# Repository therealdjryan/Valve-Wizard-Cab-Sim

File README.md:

# Valve-Wizard-Cab-Sim
http://valvewizard.co.uk/cabsim.html

[HTML BOM Viewer](https://htmlpreview.github.io/?https://raw.githubusercontent.com/therealdjryan/Valve-Wizard-Cab-Sim/main/fab/htmlbom/ibom.html)

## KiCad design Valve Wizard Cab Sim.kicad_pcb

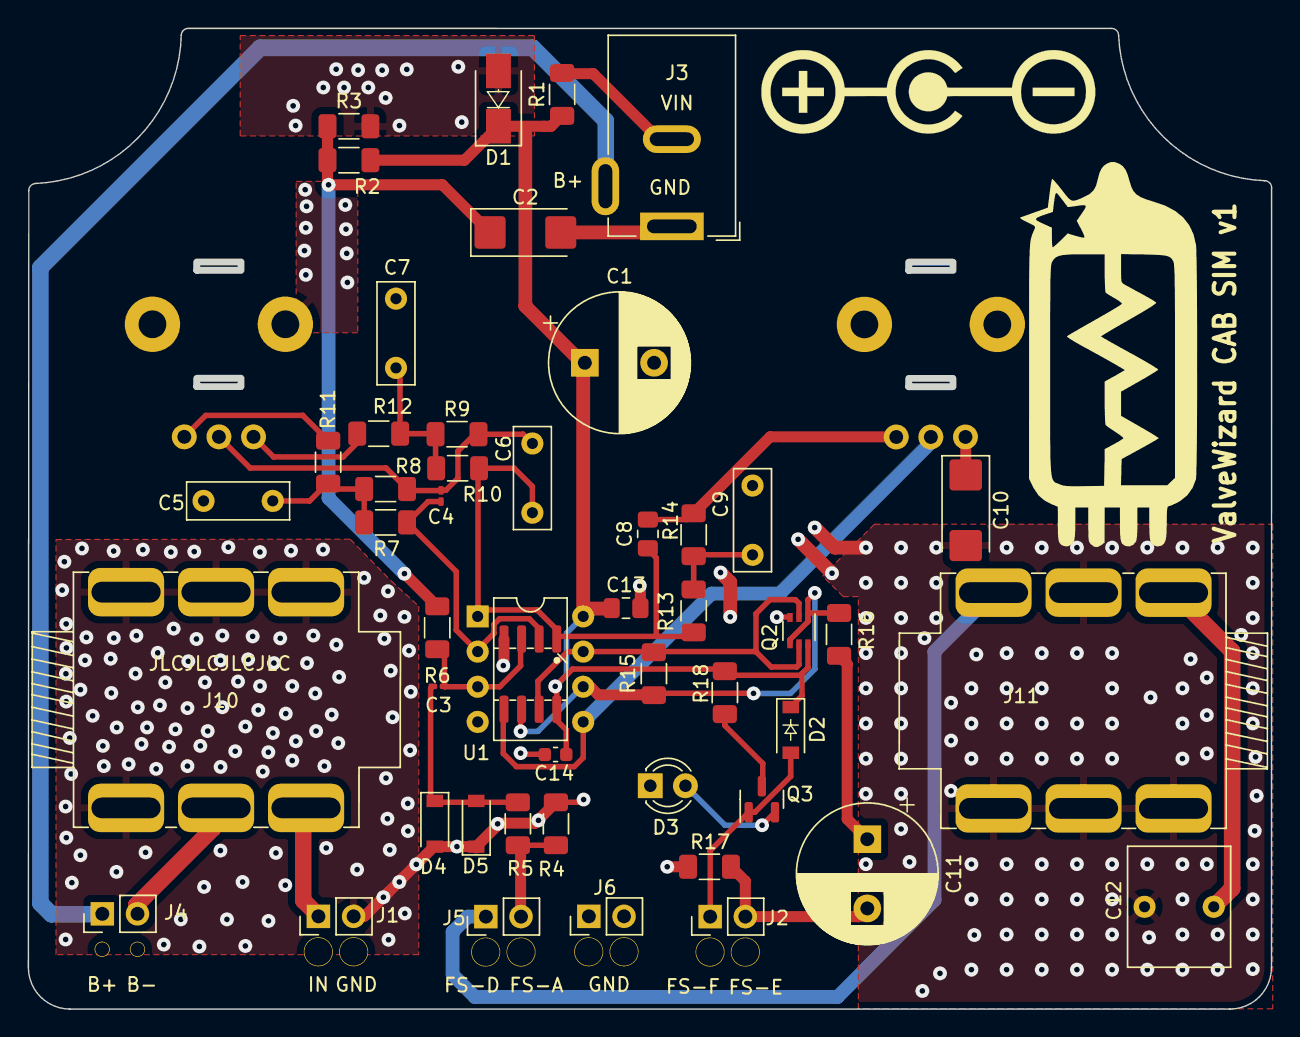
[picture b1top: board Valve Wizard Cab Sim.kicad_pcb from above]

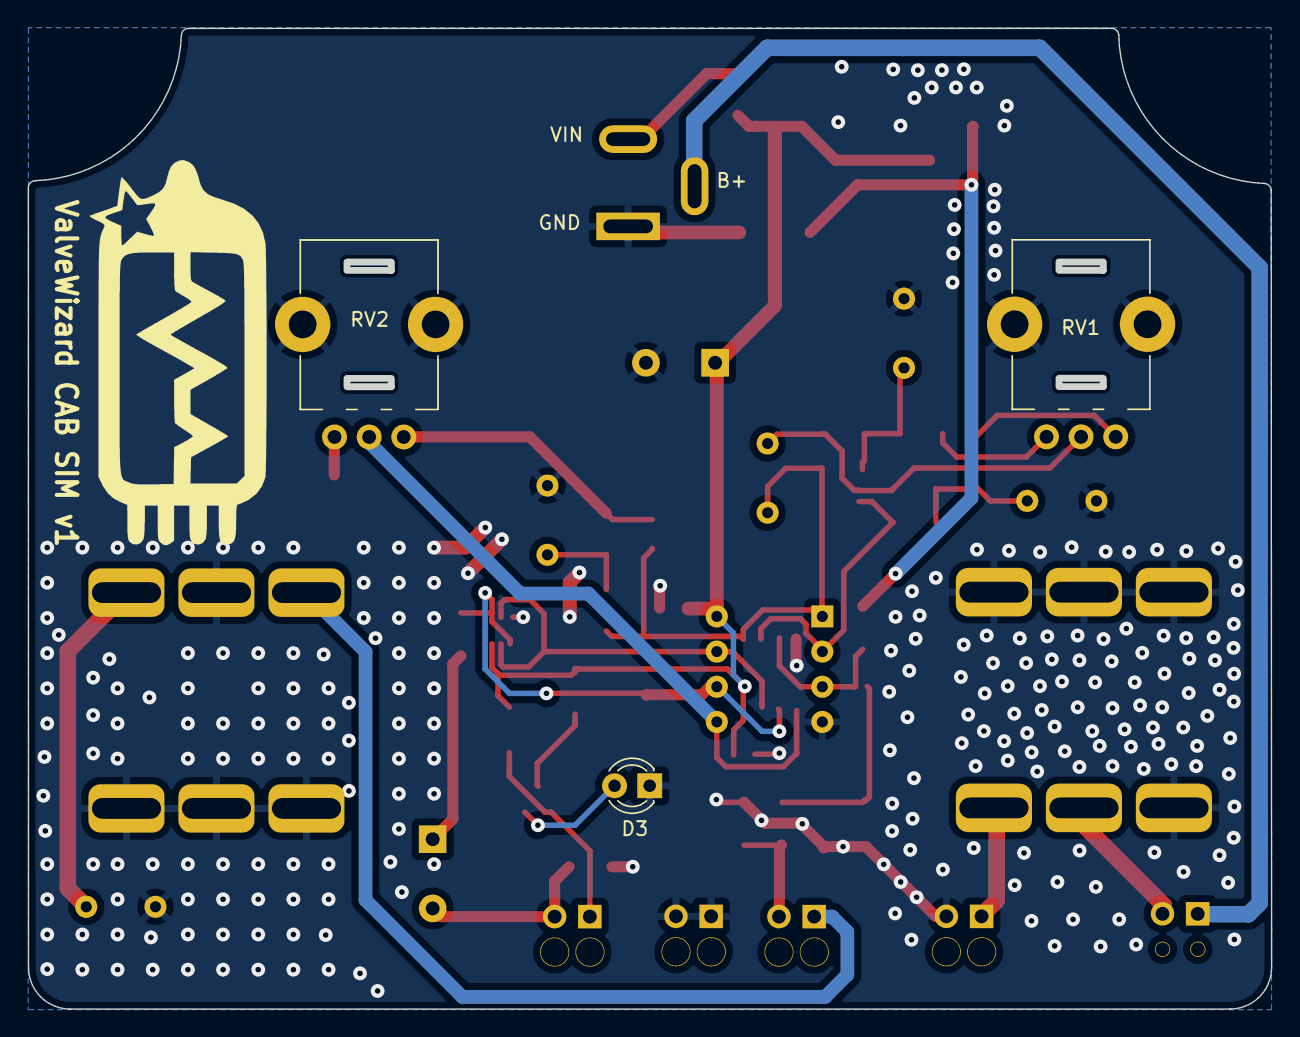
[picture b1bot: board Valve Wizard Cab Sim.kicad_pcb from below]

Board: 2 copper layers, 89.4 x 70.4 mm, 50 parts (3 on the bottom side), 30 nets.

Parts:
C1, C11: 470u; CP_Radial_D10.0mm_P5.00mm
C2, C10: 47u; CP_EIA-6032-28_Kemet-C_Pad2.25x2.35mm_HandSolder
C3: 2n2; C_0201_0603Metric_Pad0.64x0.40mm_HandSolder
C4: 1n; C_0201_0603Metric_Pad0.64x0.40mm_HandSolder
C5, C6: 22n; C_Rect_L7.2mm_W2.5mm_P5.00mm_FKS2_FKP2_MKS2_MKP2
C7: 470n; C_Rect_L7.2mm_W2.5mm_P5.00mm_FKS2_FKP2_MKS2_MKP2
C8: 220p; C_0805_2012Metric_Pad1.18x1.45mm_HandSolder
C9: 330n; C_Rect_L7.2mm_W2.5mm_P5.00mm_FKS2_FKP2_MKS2_MKP2
C12: 1u; C_Rect_L7.2mm_W8.5mm_P5.00mm_FKP2_FKP2_MKS2_MKP2
C13: 100n; C_0805_2012Metric_Pad1.18x1.45mm_HandSolder
C14: 100n; C_0603_1608Metric
D1: 1n4001; D_SMA
D2, D4, D5: 1n4148; D_SOD-123
D3: LED; LED_D3.0mm_FlatTop
J1: IN; PinHeader_1x02_P2.54mm_Vertical
J2: FS_EF; PinHeader_1x02_P2.54mm_Vertical
J3: Power; BarrelJack_GCT_DCJ200-10-A_Horizontal
J4: Battery; PinHeader_1x02_P2.54mm_Vertical
J5: FS; PinHeader_1x02_P2.54mm_Vertical
J6: GND; PinHeader_1x02_P2.54mm_Vertical
J10: IN; Jack_6.35mm_Neutrik_NMJ6HC-S_SOLDER_LUG
J11: OUT; Jack_6.35mm_Neutrik_NMJ6HC-S_SOLDER_LUG
Q2: BC846BPN; SOT-363_SC-70-6
Q3: MMBF170; SOT-23
R1, R16: 10R; R_1206_3216Metric_Pad1.30x1.75mm_HandSolder
R2, R3: 100K; R_1206_3216Metric_Pad1.30x1.75mm_HandSolder
R4, R6: 1M; R_1206_3216Metric_Pad1.30x1.75mm_HandSolder
R5, R11: 1K; R_1206_3216Metric_Pad1.30x1.75mm_HandSolder
R7, R10, R17: 10K; R_1206_3216Metric_Pad1.30x1.75mm_HandSolder
R8: 22K; R_1206_3216Metric_Pad1.30x1.75mm_HandSolder
R9: 180K; R_1206_3216Metric_Pad1.30x1.75mm_HandSolder
R12: 47K; R_1206_3216Metric_Pad1.30x1.75mm_HandSolder
R13: 330R; R_1206_3216Metric_Pad1.30x1.75mm_HandSolder
R14: 33K; R_1206_3216Metric_Pad1.30x1.75mm_HandSolder
R15: 220R; R_1206_3216Metric_Pad1.30x1.75mm_HandSolder
R18: 4K7; R_1206_3216Metric_Pad1.30x1.75mm_HandSolder
RV1: 100KB; Potentiometer_Bourns_PTV09A-1_Single_Vertical
RV2: 100KA; Potentiometer_Bourns_PTV09A-1_Single_Vertical
U1: TL072; SOIC_DIP-8

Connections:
4.5V: C2.1, R2.2, R3.1, R6.2
9V: C1.1, C13.1, C14.1, D1.1 (K), D2.1 (K), Q2.6 (C1), R1.1, R2.1, R18.1, U1.8 (V+)
/Sleeve: C12.1, J11.S
BAT+: J3.3, J4.1
BAT-: J4.2, J10.R
FS_A: J5.2, R4.1, R5.2
FS_CD: J5.1, J11.T
FS_E: C11.2, J2.2, R17.1
FS_F: D2.2 (A), J2.1, Q3.1 (G)
GND: C1.2, C2.2, C5.2, C7.2, C9.2, C10.2, C12.2, C13.2, C14.2, D1.2 (A), D3.1 (K), D4.2 (A), D5.1 (K), J1.2, J3.1, J6.1, J6.2, J10.RN, J10.S, J10.SN, J10.TN, J11.R, J11.RN, J11.SN, J11.TN, Q2.3 (C2), R3.2, R4.2, R17.2, RV1.MP (MountPin), RV2.MP (MountPin), U1.4 (V-)
IN_T: J1.1, J10.T
unnamed: C3.1, D4.1 (K), D5.2 (A), R5.1
unnamed: C3.2, R6.1, U1.3 (+)
unnamed: C4.1, R7.2, U1.2 (-)
unnamed: C4.2, C6.1, R8.1, R9.2, RV1.2
unnamed: C5.1, R7.1, R8.2, R11.2
unnamed: C6.2, C8.1, R10.1, R13.2, U1.1
unnamed: C7.1, R9.1, R10.2, R12.1
unnamed: C8.2, R14.1, RV2.1
unnamed: C9.1, R13.1, R14.2
unnamed: C10.1, RV2.3
unnamed: C11.1, R16.1
unnamed: D3.2 (A), Q3.2 (S)
unnamed: Q2.1 (E1), Q2.4 (E2), R15.1, R16.2, U1.6 (-)
unnamed: Q2.2 (B1), Q2.5 (B2), R15.2, U1.7
unnamed: Q3.3 (D), R18.2
unnamed: R11.1, RV1.1
unnamed: R12.2, RV1.3
unnamed: RV2.2, U1.5 (+)
VIN: J3.2, R1.2

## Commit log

2022-01-31 latest
